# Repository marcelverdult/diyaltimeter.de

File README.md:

# diyaltimeter.de

The idea is to create an open source altimeter for skydiving. Currently the hardware is based on standard components connected with a custom pcb. So you can just order the pcb from [JLCPCB](https://www.jlcpcb.com/) and the rest of the parts from [Aliexpress](https://aliexpress.com). The cost should be <50$ depending on the type of housing you choose. 

## Features ( incl. Wishlist)

### General

- [OTA](https://github.com/marcelverdult/diyaltimeter.de/tree/master/ota) firmware updates
- keep logbook on internal storage
  - jump number
  - exit altitude
  - ff time
  - deployment altitude
  - cp time
  - plane
  - location
  - date/time
- sync logbook via WiFi (Wishlist - needs a backend)

### Ground
- sleep mode to save energy
- check pressure every xx seconds
- wake up on button press or climb detection

### Airplane 
- date/time
- altitude
- climb rate
- time to altitude

### Freefall
- altitude
- numbers as big as possible on screen

### Canopy
- altitude
- descent rate

## Hardware:
- ESP32 ( LOLIN D32 V1.0.0 - [Aliexpress](https://www.aliexpress.com/item/WEMOS-LOLIN32-V1-0-0-wifi-bluetooth-board-based-ESP-32-4MB-FLASH/32808551116.html) ~10$
  - built in LiPo charger
- 2x BMP280 sensors [Aliexpress](https://www.aliexpress.com/item/I2C-SPI-GY-BMP280-3-3-Digital-Barometric-Pressure-Altitude-Sensor-High-Precision-Atmospheric-Module-for/32651665846.html) (make sure to get the 6 pin version! Else you can't change the I2C address of the second sensor) ~2$
- 2.42" OLED SPI display [Aliexpress](https://www.aliexpress.com/wholesale?catId=0&SearchText=2.42+oled) ~20$
- 2.500mAh LiPo battery ~10$
- D3231 RTC module [Aliexpress](https://www.aliexpress.com/wholesale?catId=0&SearchText=d3231+rtc+raspberry) ~1$
- 3 buttons ~1$
- [custom PCB ](https://github.com/marcelverdult/diyaltimeter.de/tree/master/kicad)
- 3D printed housing with wristmount

## Test setup:

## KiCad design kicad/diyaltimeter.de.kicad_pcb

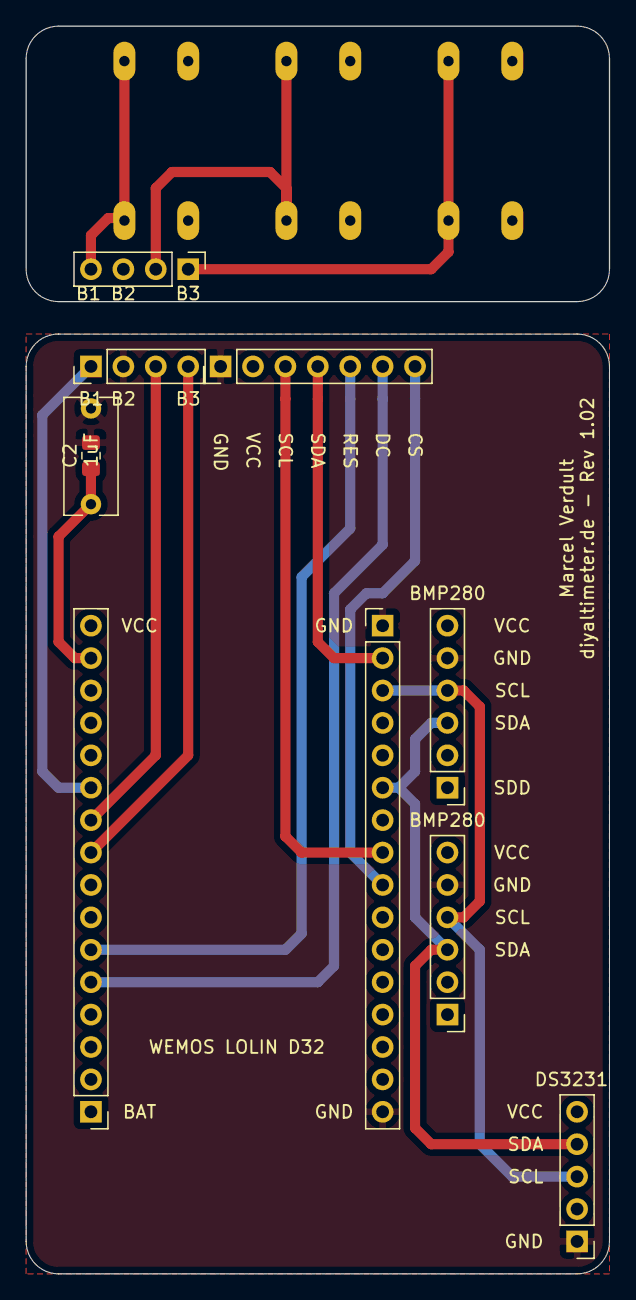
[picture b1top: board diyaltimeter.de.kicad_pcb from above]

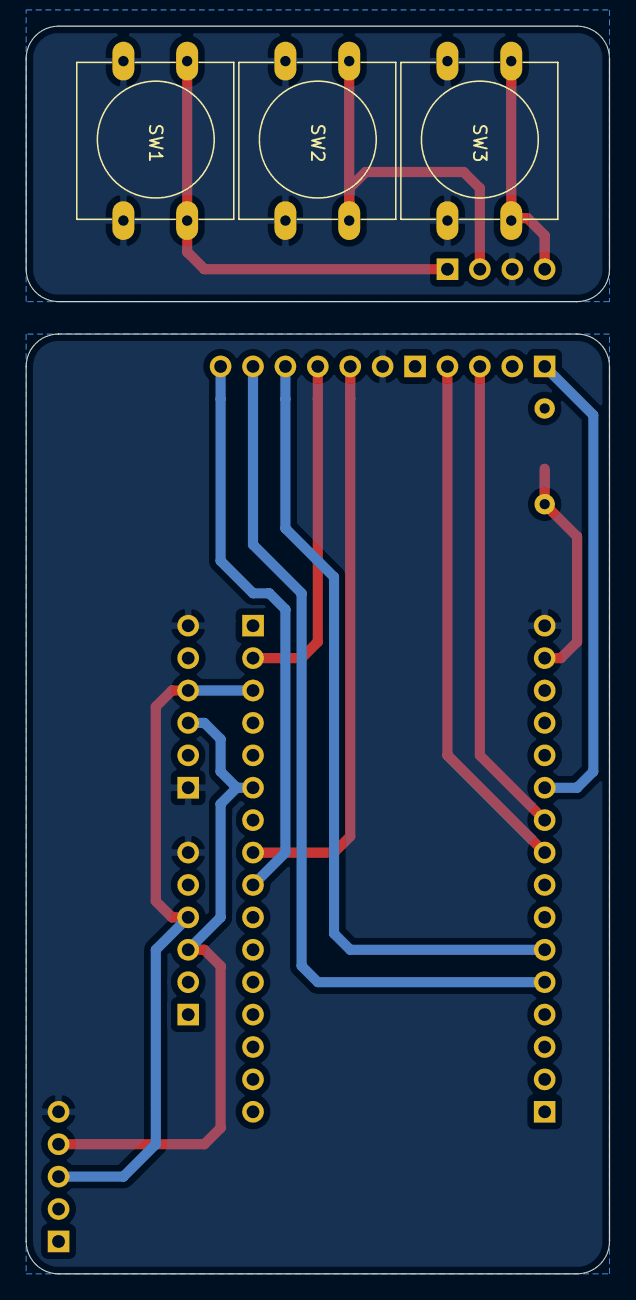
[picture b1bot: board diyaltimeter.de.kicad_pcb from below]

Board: 2 copper layers, 45.7 x 97.8 mm, 13 parts (3 on the bottom side), 17 nets.

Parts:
C1: C_Small; C_Rect_L9.0mm_W4.0mm_P7.50mm_MKT
C2: C; C_0805_2012Metric_Pad1.15x1.40mm_HandSolder
J1: Buttons; PinHeader_1x04_P2.54mm_Vertical
J2: Display; PinHeader_1x07_P2.54mm_Vertical
J3: links; PinHeader_1x16_P2.54mm_Vertical
J4: rechts; PinHeader_1x16_P2.54mm_Vertical
J5: I2C_BMP280; PinHeader_1x06_P2.54mm_Vertical
J6: I2C_BMP280_2; PinHeader_1x06_P2.54mm_Vertical
J7: RTC DS3231; PinHeader_1x05_P2.54mm_Vertical
J8: Conn_01x04_Male; PinHeader_1x04_P2.54mm_Vertical
SW1, SW2, SW3: SW_Push; SW_PUSH-12mm

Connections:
25: J1.4, J3.9
32: J1.1, J3.11
33: J1.3, J3.10
+3V3: J2.2, J3.16, J5.6, J6.1, J6.6, J7.5
CS: J2.7, J4.9
DC: J2.6, J3.5
GND: C1.2, C2.2, J1.2, J2.1, J4.1, J4.16, J5.5, J6.5, J7.1
I2C_SCL: J4.3, J5.4, J6.4, J7.3
I2C_SDA: J4.6, J5.3, J6.3, J7.4
unnamed: J8.1, SW1.2
unnamed: J8.2, SW2.2
unnamed: J8.3, SW1.1, SW2.1, SW3.1
unnamed: J8.4, SW3.2
RES: J2.5, J3.6
RS: C1.1, C2.1, J3.15
SCL: J2.3, J4.8
SDA: J2.4, J4.2

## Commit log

2019-04-23 Set theme jekyll-theme-minimal
2019-04-23 Create CNAME
2019-04-23 Rename README.md to index.md
2019-04-23 Rename index.md to README.md
2019-04-23 clean
2019-04-23 initial
2019-04-23 Update issue templates
2019-04-24 test file
2019-04-28 code structure, basic pcb layout, preview picture
2019-04-28 updated pcb
2019-04-28 Create latest
2019-04-29 pcb v1.01
2019-05-02 pcb re-leayout
2019-05-02 final pcb
2019-05-03 code v0.02
2019-05-04 code v0.1b1
2019-05-04 code for protoype
2019-05-04 uncomment testcode
2019-05-05 prototype update
2019-05-05 update prototype
2019-05-06 changed altitude diff check
2019-05-15 pin updates
